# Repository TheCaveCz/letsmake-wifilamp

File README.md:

# Let's make: WiFi Lamp

ESP8266 chip on Wemos D1 mini module that is driving WS2812 LED strip, one tactile switch for manual control.
Firmware contains HTTP REST API and Blynk platform integration for mobile app control.

More resources:
* [3D prints](stl)
* Firmware
  * [Original](firmware/lm-wifilamp) - uses [Arduino core for ESP8266](https://github.com/esp8266/Arduino), using [Blynk](https://blynk.cc) platform
  * [Tester](firmware/lm-wifilamp-test) - testing sketch
* [Hardware assembly](pictures)
* [PCB drawings](board) - simple PCB to avoid messing with lots of wires. Created in EAGLE 7.7

## Setup

### On your computer

* Install [Arduino core for ESP8266](https://github.com/esp8266/Arduino#installing-with-boards-manager) - **use version 2.4.2 or above**
* Install the [Blynk Arduino library](http://help.blynk.cc/getting-started-library-auth-token-code-examples/how-to-install-blynk-library-for-arduino)
* Install the [WiFi Manager library](https://github.com/tzapu/WiFiManager)
* Compile and upload the [firmware](firmware/lm-wifilamp)

### On your mobile phone

* Install [Blynk app](https://www.blynk.cc/getting-started/)
* Create account or log in
* Create new empty project in Blynk App
* Copy auth token from the app or your email
* Connect to the wifilamp AP
* Wait for WiFi login popup (or use browser and navigate to `http://192.168.4.1`)
* Enter WiFi credentials and auth token
* Setup the Blynk project (see next section)

### Reconfiguring or resetting lamp

* Hold button until the lamp lights up with violet color
* Connect to the wifilamp AP
* Wait for WiFi login popup (or use browser and navigate to `http://192.168.4.1`)
* Enter WiFi credentials and auth token

## Blynk project

[Check the video of creating the Blynk project](pictures/blynk-setup.mp4)

<video width="320"><source src="pictures/blynk-setup.mp4" type="video/mp4"></video>

## How it looks

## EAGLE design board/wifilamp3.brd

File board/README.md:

# Board

## Main

## Power button

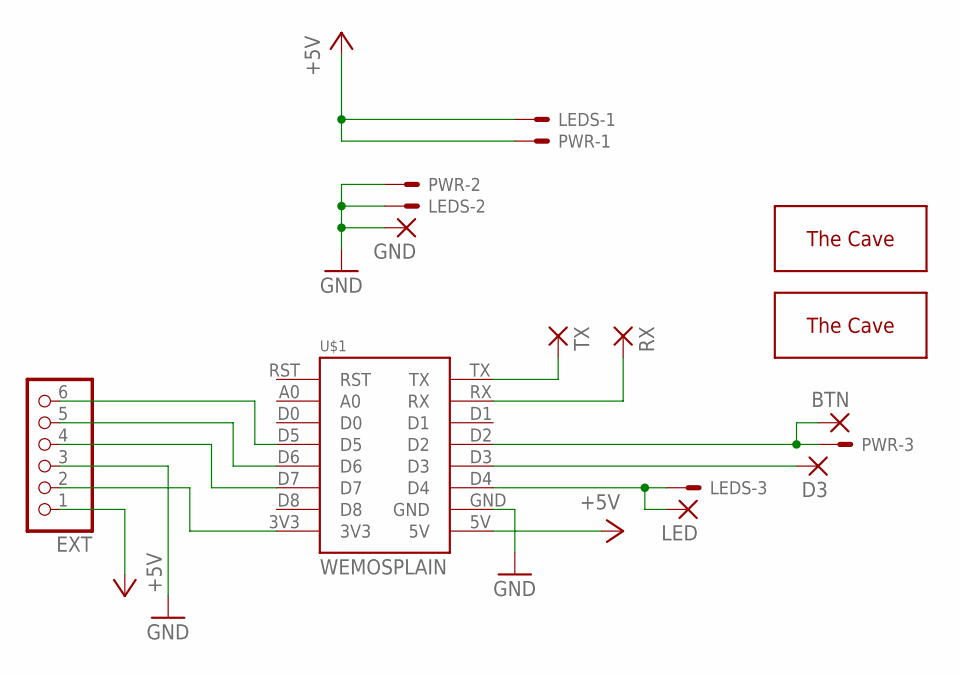
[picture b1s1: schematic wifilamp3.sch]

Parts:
BTN: WIREPADSMD1,27-254; SMD1,27-2,54
D3: WIREPADSMD1,27-254; SMD1,27-2,54
EXT: PINHD-1X6; 1X06
GND: WIREPADSMD1,27-254; SMD1,27-2,54
LED: WIREPADSMD1,27-254; SMD1,27-2,54
LEDS: JST-XH-03-PIN-LONG-PAD; JST-XH-03-PACKAGE-LONG-PAD
PWR: JST-XH-03-PIN-LONG-PAD; JST-XH-03-PACKAGE-LONG-PAD
RX: WIREPADSMD1,27-254; SMD1,27-2,54
TX: WIREPADSMD1,27-254; SMD1,27-2,54
U$1: WEMOSPLAIN; WEMOS-PLAIN
U$2: THECAVE_LOGO_TOP_MEDIUM; LOGO_TOP_MED
U$3: THECAVE_LOGO_BOTTOM_MEDIUM; LOGO_BOT_MED

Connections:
+5V: EXT.1, LEDS.1, PWR.1, U$1.5V
GND: EXT.3, GND.1, LEDS.2, PWR.2, U$1.GND
unnamed: LED.1, LEDS.3, U$1.D4
unnamed: BTN.1, PWR.3, U$1.D2
unnamed: TX.1, U$1.TX
unnamed: EXT.2, U$1.3V3
unnamed: EXT.4, U$1.D7
unnamed: EXT.5, U$1.D6
unnamed: EXT.6, U$1.D5
unnamed: RX.1, U$1.RX
unnamed: D3.1, U$1.D3

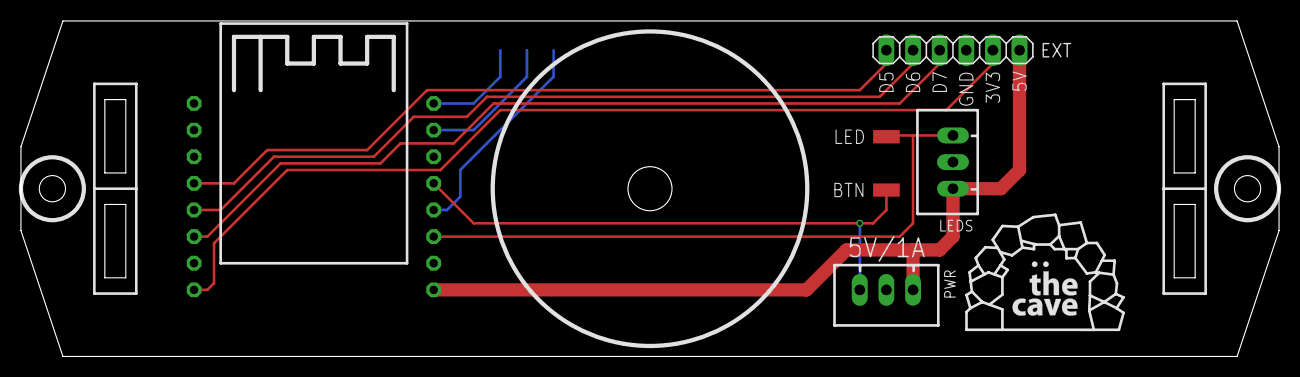
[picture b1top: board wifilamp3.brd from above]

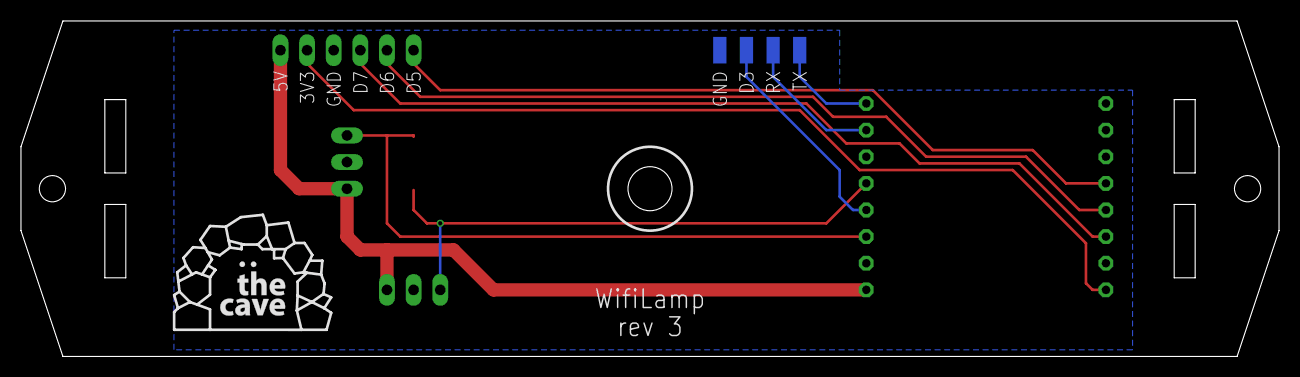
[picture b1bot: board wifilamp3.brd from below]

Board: 2 copper layers, 120.0 x 32.0 mm, 12 parts (4 on the bottom side), 11 nets.

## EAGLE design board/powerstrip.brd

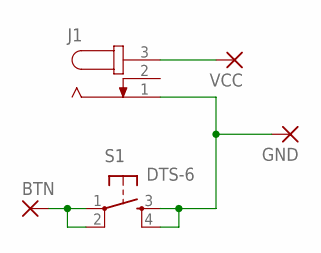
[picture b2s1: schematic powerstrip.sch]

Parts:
BTN: WIREPADSMD2,54-5,08; SMD2,54-5,08
GND: WIREPADSMD2,54-5,08; SMD2,54-5,08
J1: PC-GK210; PC-GK21
S1: DTS-6
VCC: WIREPADSMD2,54-5,08; SMD2,54-5,08

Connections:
unnamed: J1.3, VCC.1
unnamed: BTN.1, S1.1, S1.2
unnamed: GND.1, J1.1, S1.3, S1.4

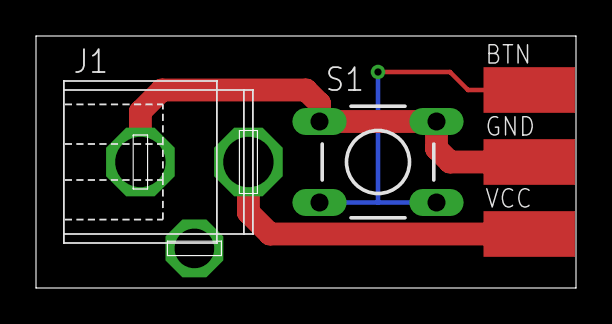
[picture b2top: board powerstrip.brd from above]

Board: 2 copper layers, 30.0 x 14.0 mm, 5 parts (0 on the bottom side), 3 nets.

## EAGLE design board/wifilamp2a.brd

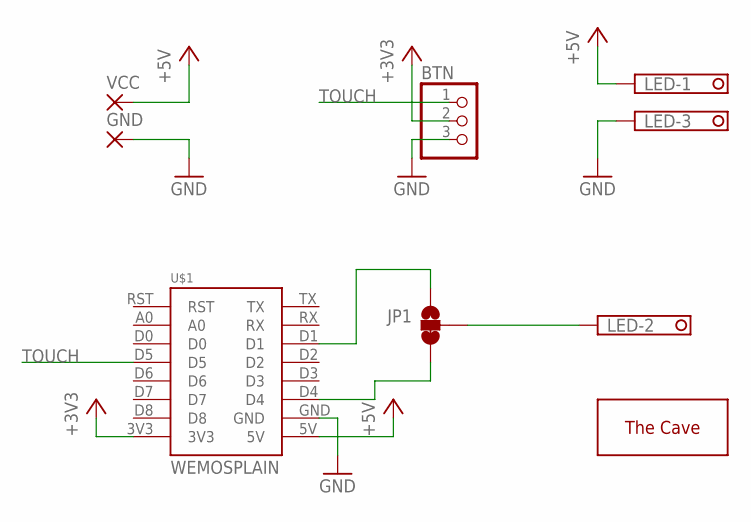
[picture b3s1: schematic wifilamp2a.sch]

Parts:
BTN: PINHD-1X3; 1X03
GND: WIREPAD3,81/1,4; 3,81/1,4
JP1: JUMPER-SMT_3_1-NC_TRACE_NO-SILK; SMT-JUMPER_3_1-NC_TRACE_NO-SILK
LED: 1751251
U$1: WEMOSPLAIN; WEMOS-PLAIN
U$2: THECAVE_LOGO_TOP_SMALL; LOGO_TOP_SMALL
VCC: PAD3,81/2

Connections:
+3V3: BTN.2, U$1.3V3
+5V: LED.1, U$1.5V, VCC.1
GND: BTN.3, GND.1, LED.3, U$1.GND
unnamed: JP1.1, U$1.D1
unnamed: JP1.3, U$1.D4
unnamed: JP1.2, LED.2
TOUCH: BTN.1, U$1.D5

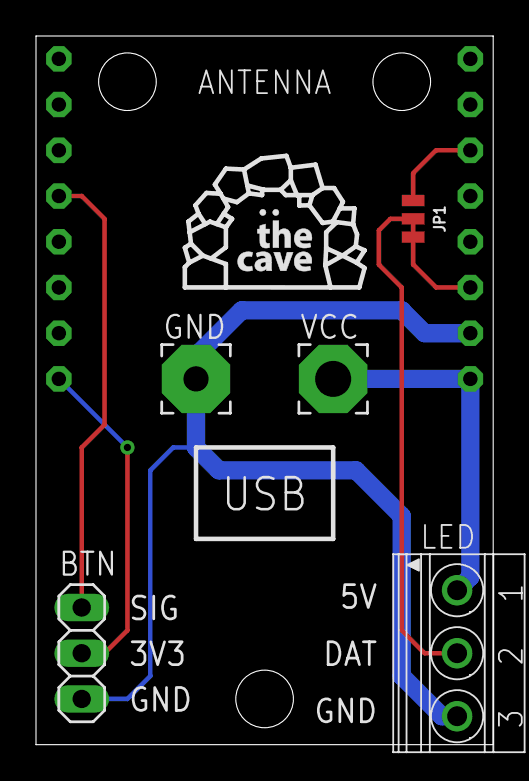
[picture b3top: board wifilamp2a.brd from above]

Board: 2 copper layers, 25.4 x 39.4 mm, 7 parts (0 on the bottom side), 7 nets.

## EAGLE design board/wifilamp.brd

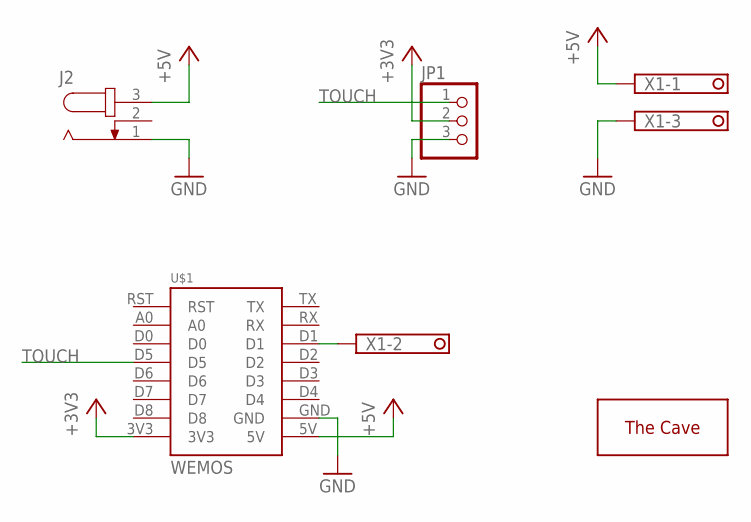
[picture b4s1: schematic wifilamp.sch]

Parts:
J2: PC-GK210; PC-GK21
JP1: PINHD-1X3; 1X03
U$1: WEMOS
U$2: THECAVE_LOGO_COPPER_SMALL; COPPER_SMALL
X1: 1751251

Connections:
+3V3: JP1.2, U$1.3V3
+5V: J2.3, U$1.5V, X1.1
GND: J2.1, JP1.3, U$1.GND, X1.3
unnamed: U$1.D1, X1.2
TOUCH: JP1.1, U$1.D5

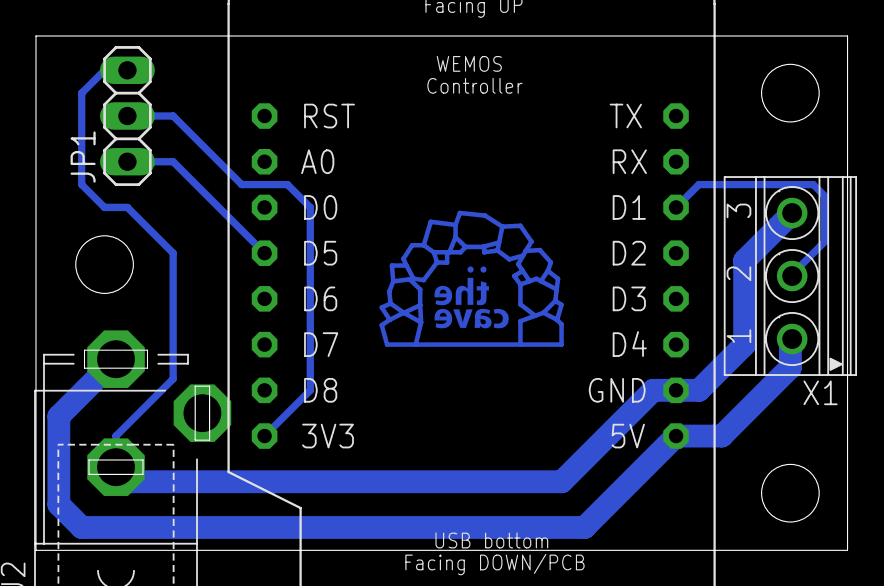
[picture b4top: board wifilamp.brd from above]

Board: 2 copper layers, 45.1 x 28.6 mm, 5 parts (1 on the bottom side), 5 nets.

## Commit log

2017-06-11 Add initial firmware
2017-06-11 Add board
2017-06-11 Add pictures
2017-06-11 Basic firmware functionality
2017-06-11 Remove TaskScheduler library, move all defines to main sketch
2017-06-11 Set OTA password
2017-06-11 Add scan endpoints
2017-06-11 Add factory reset functionality
2017-06-11 Do not log passwords
2017-06-11 Conditional logging
2017-06-12 Wait for button release before turnoff
2017-06-12 Add button debug define
2017-06-12 Better status responses
2017-06-13 Refresh led strip in each tick
2017-06-13 Add preact-boilerplate
2017-06-13 Adjusted preact-boilerplate to the needs of the project
2017-06-14 Update firmware for real content
2017-06-24 Update webpage
2017-06-25 [Web] Use superagent instead of fetch
2017-06-25 [Firmware] Use serveStatic from HTTPServer
2017-06-25 [Web] Modify overall styles
2017-06-25 [Web] Add on-off control
2017-06-27 [Web] Code cleanup
2017-08-26 [Firmware] Touch button can be disabled
2017-08-26 [Firmware] New configuration endpoint
2017-08-26 [Firmware] Add current ssid to scan response
2017-08-26 [Web] Add settings and WiFi tabs
2017-08-27 [Firmware] Convert chipId to hex
2017-08-27 [Firmware] Modify routes
2017-08-27 [Firmware] Add defines for various options
2017-08-27 [Web] Finish wifi connections, login and error handling
2017-08-27 [Firmware] Remove www-authenticate header, add packed web files
2017-08-27 [Web] Fix save button size
2017-08-27 [Web] Minor fixes
2017-08-27 [Firmware] Add SSDP and MDNS services
2017-08-28 [Web] Automatic reformat
2017-08-29 [Web] Format and cleanup
2017-08-29 [Web] Filter out identical network SSIDs
2017-08-29 [Firmware] Update web bundle
2017-08-29 [Web] Fix wifi connect bug
2017-08-29 [Firmware] User friendly mDNS instance name
2017-08-31 [Firmware] Add support for regular button
2017-08-31 [STL] Add 3d printed parts
2017-08-31 [Web] Fix inprogress state on wifi page
2017-10-08 [Firmware] Add testing sketch
2017-10-08 [App] Add iOS skeleton
2017-10-08 [Firmware] Add chipId txt record to mDNS service
2017-10-08 [Info] Update installation pictures
2017-10-13 [app] work in progress
2017-10-16 [app] color picker modifications
2017-10-20 [app] Add SwiftLint
2017-10-30 [app] Experimenting with Swinject and flows
2017-10-31 [App] Move less important files to Others folder
2017-10-31 [App] Add skeleton of setup new device flow
2017-10-31 [App] Add QR code scanning
2017-11-01 [App] WiFi lamp model added
2017-11-02 [Add] Move setup code to models
2017-11-02 [Add] Connect to lamp WiFi automatically
2017-11-03 [App] Wait for network to obtain IP address
2017-11-03 [App] Refactor device setup to AwaitKit
2017-11-03 [App] Obtain network scan results from lamp
2017-11-06 [App] Prepare architecture for network selection
2017-11-06 [App] Refactor WiFiNetwork model to protocol
2017-11-08 [App] Added list of wifi networks to select
2017-11-09 [App] Save selected WiFi network to device
2017-11-09 [App] Reboot device and wait for reboot finish
2017-11-09 [App] Setup flow dismiss after success
2017-11-12 [Firmware] OTA in test sketch
2017-11-12 [Board] update board files to rev 2
2017-11-12 [Firmware] Main sketch uses touch sensor now
2017-11-12 [Web] Convert inputs and button to proper forms
2017-11-12 [Firmware] Restart device with 6sec button press
2017-11-12 [Info] Update main picture
2017-11-12 [Info] Update main readme
2017-11-19 [STL] Remove old models and add model v2
2017-11-19 [Firmware] OTA logging in test sketch
2017-11-30 [App] Adding finctionality for controlling the device from device detail.
2017-11-30 [App] Fixing bad color setup.
2017-12-05 [App] Adding SVProgressHUD as loading indicator & temporarily changing dev team to STRV.
2017-12-05 [App] Adding general appearence setup.
2017-12-05 [App] Adding loading indicator to device detail.
2017-12-12 [Info] Update pictures
2017-12-14 [firmware] fix missing endlines in error jsons
2018-01-30 [App] Cleanup
2018-01-30 [App] Searching lamps activity indicator
2018-01-30 [App] Added Refresh devices
2018-01-31 [App] Saving Devices
2018-01-31 [App] Selecting Saved Device
2018-01-31 [App] Deleting saved devices from detail controller
2018-02-01 [App] Saving devices from table cell action
2018-02-01 [App] Destructive Remove Device option
2018-02-02 [App] Added Today Widget Target
2018-02-02 [App] Widget Data and Layout
2018-02-05 [App] Today Device Cell Layout
2018-02-05 [App] Improved Device Saving
2018-02-05 [App] Remove alert in Device Detail
2018-02-05 [App] Progress HUD for removing device
2018-02-06 [App] Rename Device
2018-02-06 [App] Open App from Widget
2018-02-06 [App] Open Detail VC from Widget
2018-02-06 [App] Added needed files to Today target
2018-02-06 [App] Today Widget with on/off commands
2018-02-07 [App] Manual Lamp Code Entry for setup
2018-02-08 [Firmware] Use UART on pin D4 for LED strip control
2018-02-09 [App] Saving colors
2018-02-09 [App] Removing saved color
2018-03-04 [board] Update board to rev 2.1
2018-04-06 Change team and bundle ids
2018-04-06 [Firmware] Add chipId record to MDNS
2018-04-07 [App] Clean up code
2018-04-07 [App] Enable swiftlint, fix warnings
2018-04-08 [Firmware] Rename cpp file for WS2812 control
2018-04-08 [Firmware] Add SSID define to test sketch
2018-04-08 [Firmware] Add Blynk enabled fw
2018-04-08 [Info] Add blynk readme
2018-04-08 [Firmware] Add WifiManager library to blynk firmware
2018-06-28 [Web] Remove web
2018-06-28 [STL] Update model files
2018-06-28 [Board] Update to rev3
2018-06-28 [Info] Update assembly instructions
2018-06-28 [Firmware] Update test sketch for rev3
2018-06-28 [Info] Add final button box photo
2018-06-28 [STL] Increase button diameter
2018-06-28 [Firmware] Update firmware to rev3
2018-06-28 [Firmware] Update pixels count
2018-08-27 [Firmware] Remove old defines, simplify connection and reset process
2018-08-27 [Firmware] Better connect/reconnect handling
2018-08-27 [Firmware] Better log messages
2018-08-28 [Firmware] Disable pixels update when blinker is running
2018-08-28 [Firmware] Improve connection handling and state logic
2018-08-28 [Firmware] Do not sync blynk on further reconnects
2018-08-29 [Info] Update assembly pictures
2018-08-29 [Firmware] Increase pulse anim range
2018-10-18 [Firmware] Added functionality to change brightness
2018-10-19 [Firmware] Set initial value to brightness and sync it
2018-10-19 [Firmware] Brightness API endpoint, add checks for brightness

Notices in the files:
parts and their libraries:
SparkFun-Jumpers: Licensing: Creative Commons ShareAlike 4.0 International - https://creativecommons.org/licenses/by-sa/4.0
